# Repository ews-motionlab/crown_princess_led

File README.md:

# crown_princess_led
LED crown princess as an educative electronics project for children

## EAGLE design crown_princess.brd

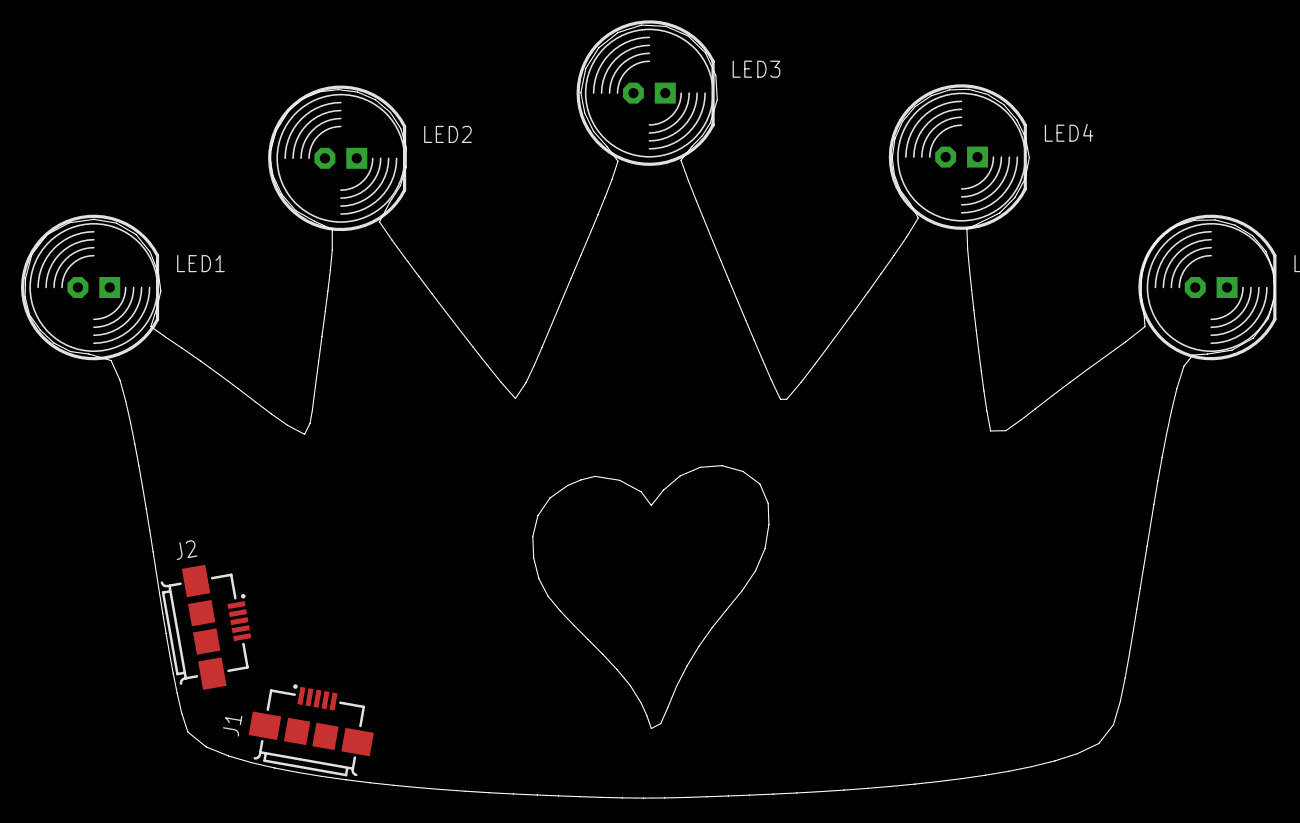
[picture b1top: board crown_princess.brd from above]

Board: 2 copper layers, 99.7 x 61.6 mm, 7 parts (0 on the bottom side), 3 nets, no tracks yet.

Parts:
J1, J2: 10104111-0001LF; FRAMATOME_10104111-0001LF
LED1, LED2, LED3, LED4, LED5: LED10MM

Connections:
GND: J1.5, J2.5
S: J1.6, J1.7, J1.8, J1.9, J2.6, J2.7, J2.8, J2.9
VBUS: J1.1, J2.1

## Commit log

2020-01-18 Create schematic and board files - Import crown outline to board file. - Add some 10mm LEDs to check fitness. - Add a couple of usbs to check possible placement.
